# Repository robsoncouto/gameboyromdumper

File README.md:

# gbcart tool (in progress)
Tool for reading data from Game Boy cartridges or the Gameboy camera. The version in the first commits work(mar 2016), but I have started to clean the code, so the present version (dec 2016) is uncomplete. 
##Description
This is a project that I started in order to backup my Gameboy saves to the PC. It also dumps roms and Gameboy camera saves. All the process that lead to this program is detailed at www.dragaosemchama.com.br/?lang=en_us
##Hardware
Schematic and layout ealge files are available, the cartridge-PC interface board uses a atmega32 and a Gameboy Color cartridge socket. The socket was salvaged from a broken gameboy. The board is connected to a PC with a USB-serial ttl cable.
##Usage
The python script is used for reading saves, roms or the cartridge header. The microcontroller code was written for a Atmega32, but can be easily ported to other microcontrollers or architectures.
##Serial library
This code uses avr-uart library kindly shared by Andy Gock based on uart library code by Peter Fleury
https://github.com/andygock/avr-uart

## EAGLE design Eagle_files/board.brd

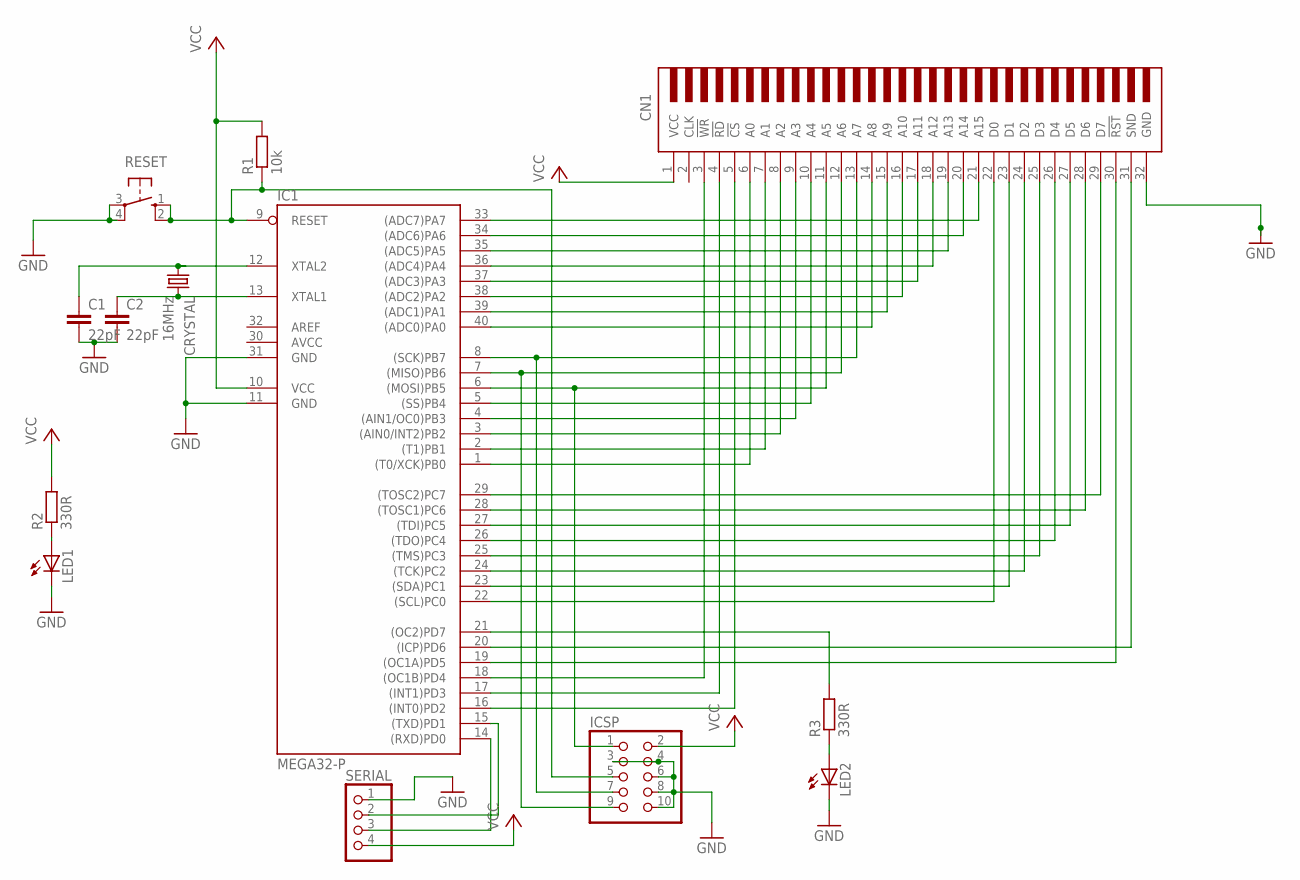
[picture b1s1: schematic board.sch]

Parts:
C1, C2: 22pF; C050-025X075
CN1: GBCONN
CRYSTAL: 16MHz; HC49/S
IC1: MEGA32-P; DIL40
ICSP: PINHD-2X5; 2X05
LED1, LED2: LED3MM
R1: 10k; 0204/7
R2, R3: 330R; 0204/7
RESET: 10-XX; B3F-10XX
SERIAL: PINHD-1X4/90; 1X04/90

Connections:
AVCC: IC1.30 (AVCC)
GND: C1.2, C2.2, CN1.32 (GND), IC1.11 (GND), IC1.31 (GND), ICSP.3, ICSP.4, ICSP.6, ICSP.8, ICSP.10, LED1.K (C), LED2.K (C), RESET.3, RESET.4 (P1), SERIAL.1
unnamed: CN1.29 (D7), IC1.29 ((TOSC2)PC7)
unnamed: CN1.28 (D6), IC1.28 ((TOSC1)PC6)
unnamed: CN1.27 (D5), IC1.27 ((TDI)PC5)
unnamed: CN1.26 (D4), IC1.26 ((TDO)PC4)
unnamed: CN1.25 (D3), IC1.25 ((TMS)PC3)
unnamed: CN1.24 (D2), IC1.24 ((TCK)PC2)
unnamed: CN1.23 (D1), IC1.23 ((SDA)PC1)
unnamed: CN1.22 (D0), IC1.22 ((SCL)PC0)
unnamed: CN1.21 (A15), IC1.33 ((ADC7)PA7)
unnamed: CN1.20 (A14), IC1.34 ((ADC6)PA6)
unnamed: CN1.19 (A13), IC1.35 ((ADC5)PA5)
unnamed: CN1.18 (A12), IC1.36 ((ADC4)PA4)
unnamed: CN1.17 (A11), IC1.37 ((ADC3)PA3)
unnamed: CN1.16 (A10), IC1.38 ((ADC2)PA2)
unnamed: CN1.15 (A9), IC1.39 ((ADC1)PA1)
unnamed: CN1.14 (A8), IC1.40 ((ADC0)PA0)
unnamed: CN1.13 (A7), IC1.8 ((SCK)PB7), ICSP.7
unnamed: CN1.12 (A6), IC1.7 ((MISO)PB6), ICSP.9
unnamed: CN1.11 (A5), IC1.6 ((MOSI)PB5), ICSP.1
unnamed: CN1.10 (A4), IC1.5 ((SS)PB4)
unnamed: CN1.9 (A3), IC1.4 ((AIN1/OC0)PB3)
unnamed: CN1.8 (A2), IC1.3 ((AIN0/INT2)PB2)
unnamed: CN1.7 (A1), IC1.2 ((T1)PB1)
unnamed: CN1.6 (A0), IC1.1 ((T0/XCK)PB0)
unnamed: CN1.30 (!RST), IC1.19 ((OC1A)PD5)
unnamed: CN1.4 (!RD), IC1.17 ((INT1)PD3)
unnamed: CN1.5 (!CS), IC1.16 ((INT0)PD2)
unnamed: LED1.A, R2.1
unnamed: CN1.31 (SND), IC1.20 ((ICP)PD6)
unnamed: C1.1, CRYSTAL.1, IC1.12 (XTAL2)
unnamed: C2.1, CRYSTAL.2, IC1.13 (XTAL1)
unnamed: CN1.3 (!WR), IC1.18 ((OC1B)PD4)
unnamed: LED2.A, R3.1
unnamed: IC1.21 ((OC2)PD7), R3.2
unnamed: IC1.9 (RESET), ICSP.5, R1.1, RESET.1 (S), RESET.2 (S1)
unnamed: IC1.15 ((TXD)PD1), SERIAL.2
unnamed: IC1.14 ((RXD)PD0), SERIAL.3
VCC: CN1.1 (VCC), IC1.10 (VCC), ICSP.2, R1.2, R2.2, SERIAL.4

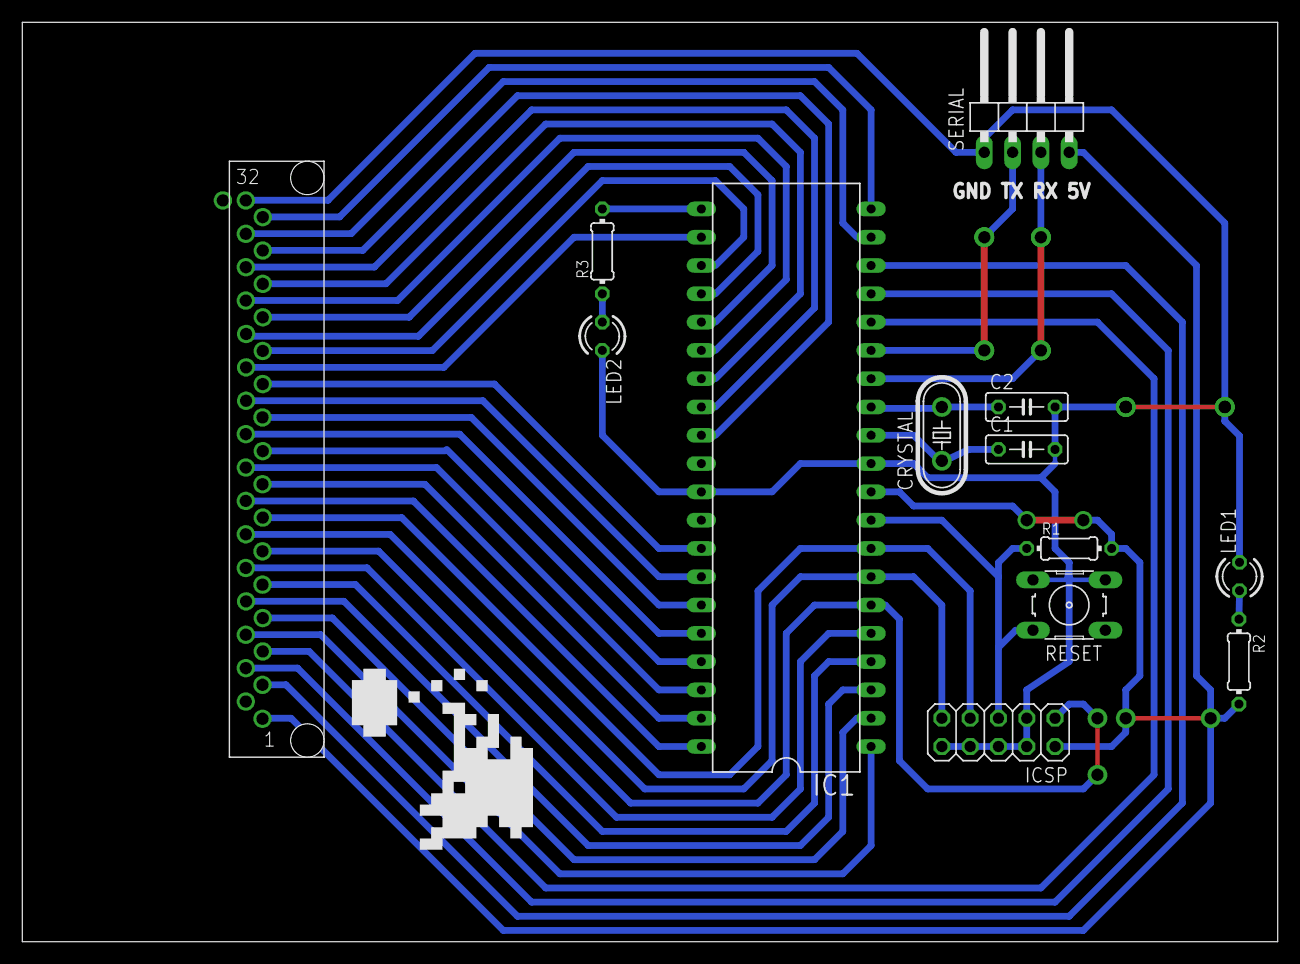
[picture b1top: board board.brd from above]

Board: 2 copper layers, 112.7 x 82.5 mm, 13 parts (0 on the bottom side), 39 nets.

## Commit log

2016-06-18 Script added to project
2016-06-18 winsoud removed for compatibility
2016-09-15 Added main file
2016-09-15 Added serial library by Peter Fleury
2016-09-15 Added constants file
2016-09-15 Added ealge files
2016-11-23 Fixed serial library location
2016-11-23 Ops, apparently I forgte that I already had mbc3 code
2016-12-19 Added a new Makefile
2016-12-19 Removing compiled files
2016-12-19 Started working on code for writing saves
2016-12-19 Separated functions from main file
2016-12-19 updated Makefile and main
2016-12-19 removed compiled uart library
2016-12-19 Fixed warnings
2016-12-20 continuing code cleaning
2016-12-20 In progress, use old versions
2016-12-20 Added a select bank function
2016-12-20 new readRAM() function
2016-12-20 Edited Makefile for colorised diagnostics
2016-12-20 Rewrote code for use of new functions
2016-12-20 Added ascii art and serial port exception to pyhton script
2016-12-21 Removing uart library from main...
2016-12-21 Added code for getting rom and ram size from cartridge
2016-12-21 Added readROM function
2016-12-21 updated main
2016-12-21 minor fixes
2016-12-22 Serial seems to be working again
2016-12-22 MBC1 ROM works fine
2016-12-23 SelectBank not working
2016-12-23 MBC1 saves working
2016-12-23 Updated READ.md on github
2016-12-24 MBC3 Rom dump working
2016-12-24 Fixed python script functions order
2016-12-24 MBC3 ok
2016-12-24 added code for save upload
2016-12-24 Error checking for save upload seems to be workin. Needs more tests
2016-12-24 A bug is crashing the board, probrably serial library, but yet to check
2016-12-25 See last commit. Aparently no software issue, there was a broken track in my board
2016-12-25 A problem in the board probrably caused a problem in the board. It took me much time to realise what was the problem, because I thought it was software. Now the serial link seems to be ok again
2016-12-25 Added a small delay between calls to serial write. This stopped the board from glitching
2016-12-26 Bug in serial library, changed to updatep version by Andy Gock
2016-12-26 Updated README.md
    Changed serial library
2016-12-26 Fixed code for writing dat to RAM
2016-12-26 Save upload working, tested on MBC1
2016-12-26 Added a function for writing data to flash ROM
2016-12-26 Fixed addres size for ROM
2016-12-27 Flashing confirmed to work
2016-12-27 There is data overlap in the code, probrably a problem with bank selecting
2016-12-27 Fixed problem with ROM address size, but bugs still persist
